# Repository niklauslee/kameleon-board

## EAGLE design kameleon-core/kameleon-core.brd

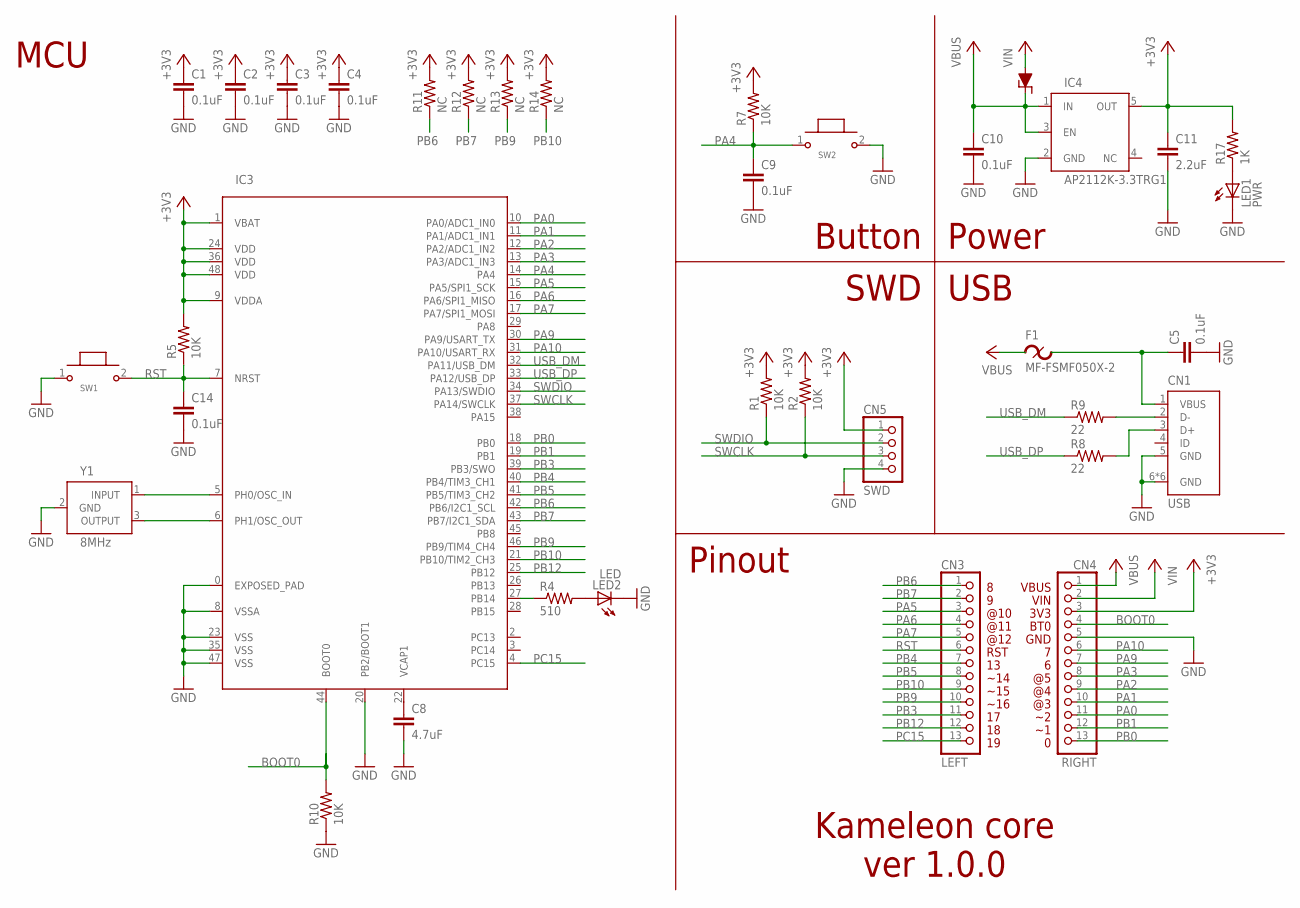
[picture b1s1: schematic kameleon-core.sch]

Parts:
C1, C2, C3, C4, C5, C9, C10, C14: 0.1uF; 1608
C8: 4.7uF; 2012
C11: 2.2uF; 2012
CN1: USB; 1050170001
CN3: LEFT; 1X13
CN4: RIGHT; 1X13
CN5: SWD; 1X04
D1: MBR120VLSF; SOD-123FL
F1: MF-FSMF050X-2; 1608
IC3: STM32F411CE/UFQFPN48; UFQFPN48
IC4: AP2112K-3.3TRG1; SOT25
LED1: PWR; D1608
LED2: LED; D1608
R1, R2, R5, R7, R10: 10K; 1608
R4: 510; 1608
R8, R9: 22; 1608
R11, R12, R13, R14: NC; 1608
R17: 1K; 1608
SW1: NRST; NW3-A03-05
SW2: BTN; NW3-A03-05
Y1: 8MHz; R0

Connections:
+3V3: C1.1, C2.1, C3.1, C4.1, C11.1, CN4.3, CN5.1, IC3.1 (VBAT), IC3.9 (VDDA), IC3.24 (VDD), IC3.36 (VDD), IC3.48 (VDD), IC4.5 (OUT), R1.2, R2.2, R5.2, R7.2, R11.2, R12.2, R13.2, R14.2, R17.2
BOOT0: CN4.4, IC3.44 (BOOT0), R10.2
GND: C1.2, C2.2, C3.2, C4.2, C5.2, C8.2, C9.2, C10.2, C11.2, C14.2, CN1.5 (GND), CN1.6 (GND), CN1.7 (GND), CN1.8 (GND), CN1.9 (GND), CN1.10 (GND), CN1.11 (GND), CN4.5, CN5.4, IC3.0 (EXPOSED_PAD), IC3.8 (VSSA), IC3.20 (PB2/BOOT1), IC3.23 (VSS), IC3.35 (VSS), IC3.47 (VSS), IC4.2 (GND), LED1.2 (C), LED2.2 (C), R10.1, SW1.1, SW2.2, Y1.2 (GND)
unnamed: C8.1, IC3.22 (VCAP1)
unnamed: IC3.5 (PH0/OSC_IN), Y1.1 (INPUT)
unnamed: IC3.6 (PH1/OSC_OUT), Y1.3 (OUTPUT)
unnamed: CN1.2 (D-), R9.2
unnamed: IC3.27 (PB14), R4.1
unnamed: LED2.1 (A), R4.2
unnamed: CN1.3 (D+), R8.2
unnamed: C5.1, CN1.1 (VBUS), F1.2
unnamed: LED1.1 (A), R17.1
PA0: CN4.11, IC3.10 (PA0/ADC1_IN0)
PA1: CN4.10, IC3.11 (PA1/ADC1_IN1)
PA2: CN4.9, IC3.12 (PA2/ADC1_IN2)
PA3: CN4.8, IC3.13 (PA3/ADC1_IN3)
PA4: C9.1, IC3.14 (PA4), R7.1, SW2.1
PA5: CN3.3, IC3.15 (PA5/SPI1_SCK)
PA6: CN3.4, IC3.16 (PA6/SPI1_MISO)
PA7: CN3.5, IC3.17 (PA7/SPI1_MOSI)
PA9: CN4.7, IC3.30 (PA9/USART_TX)
PA10: CN4.6, IC3.31 (PA10/USART_RX)
PB0: CN4.13, IC3.18 (PB0)
PB1: CN4.12, IC3.19 (PB1)
PB3: CN3.11, IC3.39 (PB3/SWO)
PB4: CN3.7, IC3.40 (PB4/TIM3_CH1)
PB5: CN3.8, IC3.41 (PB5/TIM3_CH2)
PB6: CN3.1, IC3.42 (PB6/I2C1_SCL), R11.1
PB7: CN3.2, IC3.43 (PB7/I2C1_SDA), R12.1
PB9: CN3.10, IC3.46 (PB9/TIM4_CH4), R13.1
PB10: CN3.9, IC3.21 (PB10/TIM2_CH3), R14.1
PB12: CN3.12, IC3.25 (PB12)
PC15: CN3.13, IC3.4 (PC15)
RST: C14.1, CN3.6, IC3.7 (NRST), R5.1, SW1.2
SWCLK: CN5.3, IC3.37 (PA14/SWCLK), R2.1
SWDIO: CN5.2, IC3.34 (PA13/SWDIO), R1.1
USB_DM: IC3.32 (PA11/USB_DM), R9.1
USB_DP: IC3.33 (PA12/USB_DP), R8.1
VBUS: C10.1, CN4.1, D1.2, F1.1, IC4.1 (IN), IC4.3 (EN)
VIN: CN4.2, D1.1

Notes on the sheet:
Power
Button
SWD
USB
MCU
Pinout
VBUS VIN 3V3 BT0 GND 7 6 @5 @4 @3 ~2 ~1 0
8 9 @10 @11 @12 RST 13 ~14 ~15 ~16 17 18 19
Kameleon core ver 1.0.0

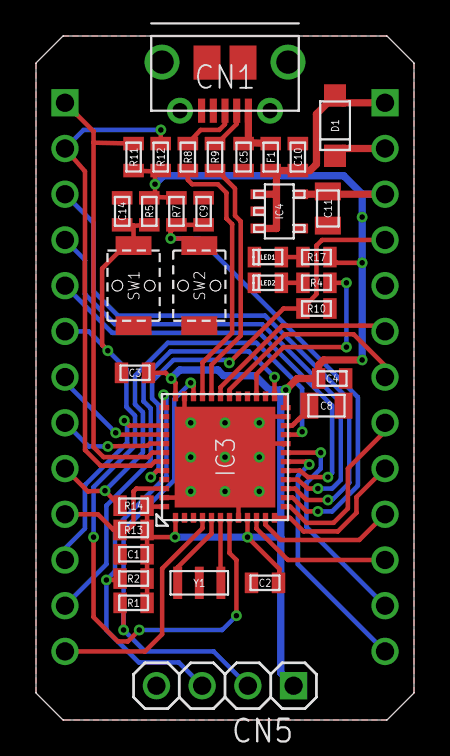
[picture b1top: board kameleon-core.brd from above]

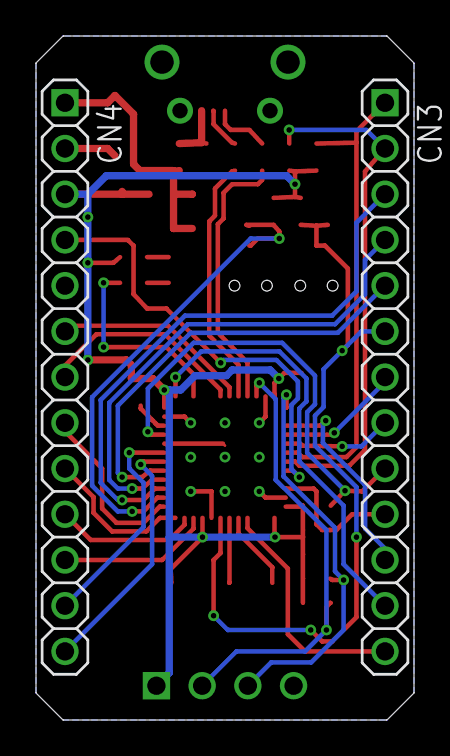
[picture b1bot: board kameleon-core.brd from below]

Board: 2 copper layers, 21.0 x 38.0 mm, 37 parts (3 on the bottom side), 40 nets.

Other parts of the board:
U$1: LOGO_VECTOR

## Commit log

2018-10-10 Kameleon Core board
2019-09-07 Eagle cad update - New format of the latest Eable cad
2019-09-07 Change R10 value to 10K
2019-09-07 Remove R3 and R6 because it's not needed
2019-09-08 Change CN3 and CN4 from Top to Bottom. - Resolve the issue #3
2019-09-10 I2C pull-ups are changed from 10K to NC
2019-09-12 Adding schematic of the Kameleon-core V1.0 board
2019-09-13 Board name changed in English Version is changed to 1.0.0
2019-11-07 Fix the unexpected change on the 3v3 wire on the bottom. - Resolve the issue #7
